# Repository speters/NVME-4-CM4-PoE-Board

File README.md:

# CM4-IO-POE-4G PCIEx1 to NVME Adapter

This is an NVME (M-key) adapter board for the PCIEx1 slot.

Its PCB is designed with a break-away section for the fingered connector. This is then soldered in a matching slot of the PCB to form a 90 degree connector.

## Revisions

 * 0.9.0 added oscillator for 32.768kHz SUSClk signal

 * 0.8.2 finger board improvements, minor size adjustments

 * 0.8.1 working version, gone into small production run

## Description

PCB of the 0.8.2 version without SUSClk

It is designed to fit the [Waveshare CM4G-IO-POE-4G-BOX](https://www.waveshare.com/wiki/Compute_Module_4_PoE_4G_Board#Isolation_GPIO.2FI2C).

## Building

The PCB is cost-optimized to be produced by services like JLCPCB.

You have to separate the finger board from the PCB and solder it into its slot.
Make sure the finger board is at right angles to the main PCB when soldering.

An NVME M-key connector, a standoff, and screw for mounting the NVME has to be provided.
It is recommended to fix the board to the CM4 board with standoffs, not rely solely on the PCIEx1 connector to hold everything in place. For doing this, there are two holes matching holes in the baseboard PCB.

The adapter seems to work fine on the CM4 board without fitting the passives (capacitors and LED).

Remember that your kernel needs PCIe support. There is a convenient [docker cross-compile environment by Jeff Geerling](https://github.com/geerlingguy/raspberry-pi-pcie-devices/tree/master/extras/cross-compile).

## Improvement ideas

 * choose gold fingers for production (I went as cheap as possible with HASL)

 * get out of the way for the CAM0 FPC cable

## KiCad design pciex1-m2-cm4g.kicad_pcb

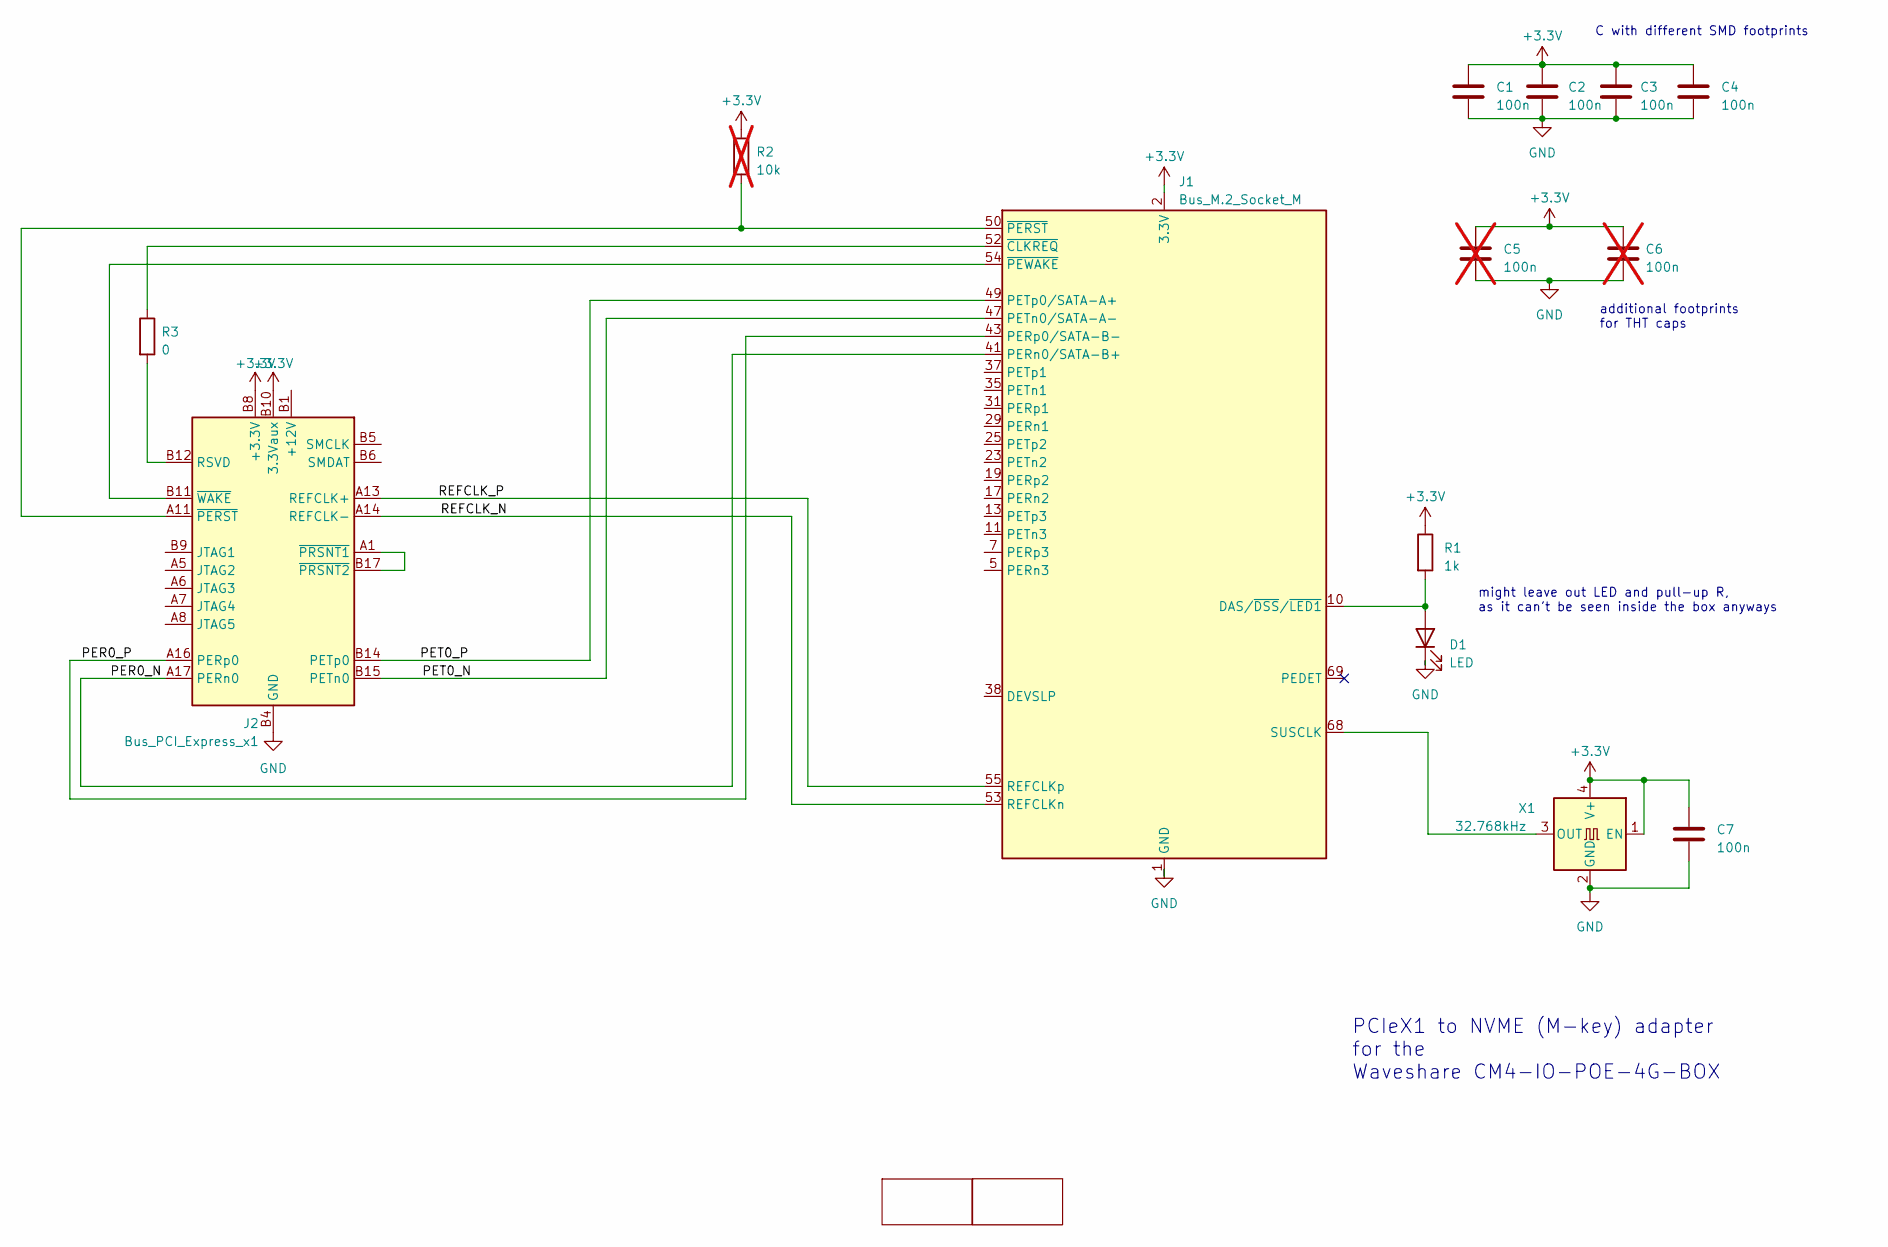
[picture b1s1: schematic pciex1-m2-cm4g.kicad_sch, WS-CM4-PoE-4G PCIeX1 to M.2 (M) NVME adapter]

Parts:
C1, C2, C3, C7: 100n; C_1206_3216Metric
C4: 100n; C_0603_1608Metric
C5, C6: 100n; C_Disc_D3.0mm_W1.6mm_P2.50mm; not fitted
D1: LED; LED_0805_2012Metric
J1: Bus_M.2_Socket_M; TE_1-2199230-6 M2 2280; PartGroup Card Edge Connectors; JLCPCB C841651
J2: Bus_PCI_Express_x1; BUS_PCIexpress_x1 hor_1
R1: 1k; R_0603_1608Metric
R2: 10k; R_0603_1608Metric; not fitted
R3: 0; R_0603_1608Metric
X1: 32.768kHz; Oscillator_SMD_EuroQuartz_XO32-4Pin_3.2x2.5mm; JLCPCB C2901582

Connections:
+3.3V: C1.1, C2.1, C3.1, C4.1, C5.1, C6.1, C7.1, J1.2 (3.3V), J1.4 (3.3V), J1.12 (3.3V), J1.14 (3.3V), J1.16 (3.3V), J1.18 (3.3V), J1.70 (3.3V), J1.72 (3.3V), J1.74 (3.3V), J2.A9 (+3.3V), J2.A10 (+3.3V), J2.B8 (+3.3V), J2.B10 (3.3Vaux), R1.1, R2.1, X1.1 (EN), X1.4 (V+); also elsewhere on the board
/PER0_N: J1.41 (PERn0/SATA-B+), J2.A17 (PERn0)
/PER0_P: J1.43 (PERp0/SATA-B-), J2.A16 (PERp0)
/PET0_N: J1.47 (PETn0/SATA-A-), J2.B15 (PETn0)
/PET0_P: J1.49 (PETp0/SATA-A+), J2.B14 (PETp0)
/REFCLK_N: J1.53 (REFCLKn), J2.A14 (REFCLK-)
/REFCLK_P: J1.55 (REFCLKp), J2.A13 (REFCLK+)
GND: C1.2, C2.2, C3.2, C4.2, C5.2, C6.2, C7.2, D1.1 (K), J1.1 (GND), J1.3 (GND), J1.9 (GND), J1.15 (GND), J1.21 (GND), J1.27 (GND), J1.33 (GND), J1.39 (GND), J1.45 (GND), J1.51 (GND), J1.57 (GND), J1.71 (GND), J1.73 (GND), J1.75 (GND), J2.A4 (GND), J2.A12 (GND), J2.A15 (GND), J2.A18 (GND), J2.B4 (GND), J2.B7 (GND), J2.B13 (GND), J2.B16 (GND), J2.B18 (GND), X1.2 (GND); also elsewhere on the board
unnamed: D1.2 (A), J1.10 (DAS/~DSS/~LED1), R1.2
unnamed: J1.68 (SUSCLK), X1.3 (OUT)
unnamed: J1.52 (~CLKREQ), R3.1
unnamed: J1.50 (~PERST), J2.A11 (~PERST), R2.2
unnamed: J1.54 (~PEWAKE), J2.B11 (~WAKE)
unnamed: J2.A2 (+12V), J2.A3 (+12V), J2.B1 (+12V), J2.B2 (+12V), J2.B3 (+12V)
unnamed: J2.B12 (RSVD), R3.2
unnamed: J2.A1 (~PRSNT1), J2.B17 (~PRSNT2)

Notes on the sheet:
C with different SMD footprints
PCIeX1 to NVME (M-key) adapter for the Waveshare CM4-IO-POE-4G-BOX
additional footprints for THT caps
might leave out LED and pull-up R, as it can't be seen inside the box anyways

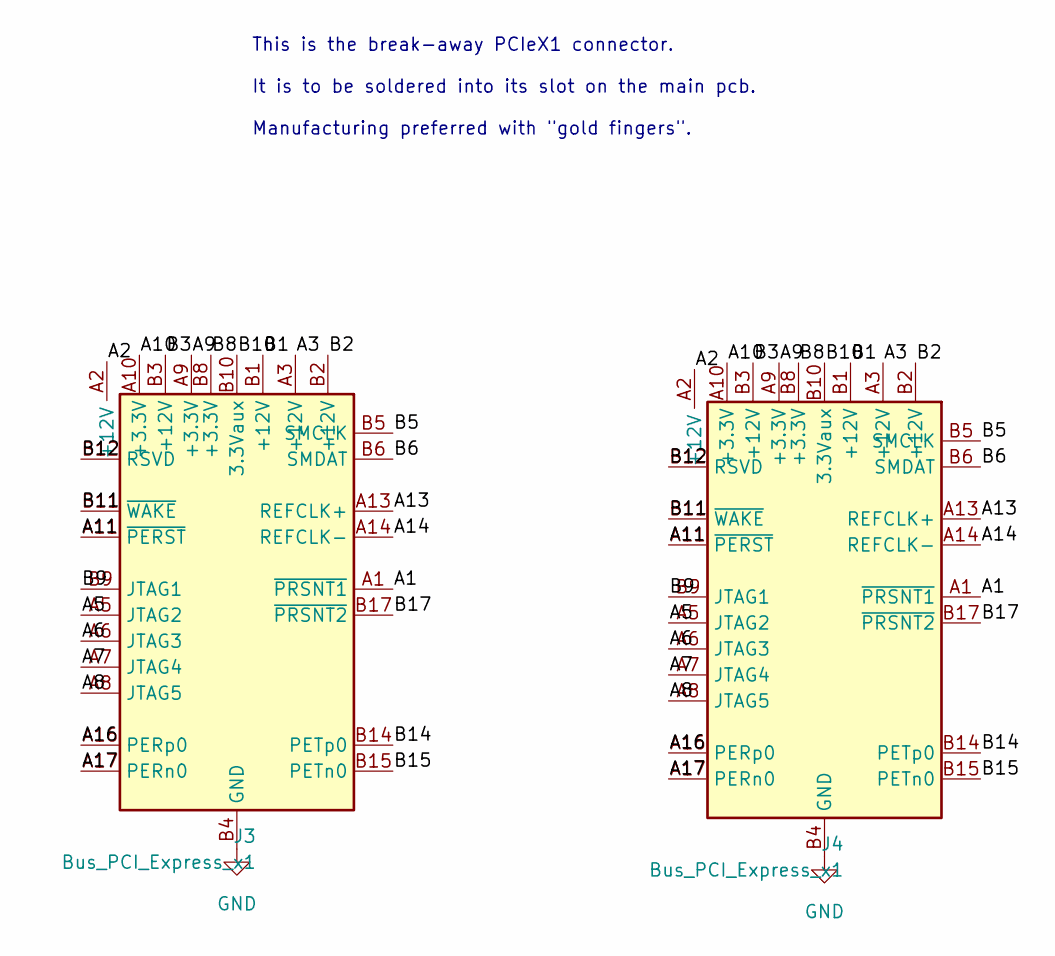
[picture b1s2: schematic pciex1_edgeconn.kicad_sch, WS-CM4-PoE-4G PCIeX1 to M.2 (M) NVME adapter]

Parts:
J3: Bus_PCI_Express_x1; BUS_PCIexpress_x1
J4: Bus_PCI_Express_x1; BUS_PCIexpress_x1 SOLDER

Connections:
/pciex1_edgeconn/A1: J3.A1 (~PRSNT1), J4.A1 (~PRSNT1)
/pciex1_edgeconn/A2: J3.A2 (+12V), J4.A2 (+12V)
/pciex1_edgeconn/A3: J3.A3 (+12V), J4.A3 (+12V)
/pciex1_edgeconn/A5: J3.A5 (JTAG2), J4.A5 (JTAG2)
/pciex1_edgeconn/A6: J3.A6 (JTAG3), J4.A6 (JTAG3)
/pciex1_edgeconn/A7: J3.A7 (JTAG4), J4.A7 (JTAG4)
/pciex1_edgeconn/A8: J3.A8 (JTAG5), J4.A8 (JTAG5)
/pciex1_edgeconn/A9: J3.A9 (+3.3V), J4.A9 (+3.3V)
/pciex1_edgeconn/A10: J3.A10 (+3.3V), J4.A10 (+3.3V)
/pciex1_edgeconn/A11: J3.A11 (~PERST), J4.A11 (~PERST)
/pciex1_edgeconn/A13: J3.A13 (REFCLK+), J4.A13 (REFCLK+)
/pciex1_edgeconn/A14: J3.A14 (REFCLK-), J4.A14 (REFCLK-)
/pciex1_edgeconn/A16: J3.A16 (PERp0), J4.A16 (PERp0)
/pciex1_edgeconn/A17: J3.A17 (PERn0), J4.A17 (PERn0)
/pciex1_edgeconn/B1: J3.B1 (+12V), J4.B1 (+12V)
/pciex1_edgeconn/B2: J3.B2 (+12V), J4.B2 (+12V)
/pciex1_edgeconn/B3: J3.B3 (+12V), J4.B3 (+12V)
/pciex1_edgeconn/B5: J3.B5 (SMCLK), J4.B5 (SMCLK)
/pciex1_edgeconn/B6: J3.B6 (SMDAT), J4.B6 (SMDAT)
/pciex1_edgeconn/B8: J3.B8 (+3.3V), J4.B8 (+3.3V)
/pciex1_edgeconn/B9: J3.B9 (JTAG1), J4.B9 (JTAG1)
/pciex1_edgeconn/B10: J3.B10 (3.3Vaux), J4.B10 (3.3Vaux)
/pciex1_edgeconn/B11: J3.B11 (~WAKE), J4.B11 (~WAKE)
/pciex1_edgeconn/B12: J3.B12 (RSVD), J4.B12 (RSVD)
/pciex1_edgeconn/B14: J3.B14 (PETp0), J4.B14 (PETp0)
/pciex1_edgeconn/B15: J3.B15 (PETn0), J4.B15 (PETn0)
/pciex1_edgeconn/B17: J3.B17 (~PRSNT2), J4.B17 (~PRSNT2)
GND: J3.A4 (GND), J3.A12 (GND), J3.A15 (GND), J3.A18 (GND), J3.B4 (GND), J3.B7 (GND), J3.B13 (GND), J3.B16 (GND), J3.B18 (GND), J4.A4 (GND), J4.A12 (GND), J4.A15 (GND), J4.A18 (GND), J4.B4 (GND), J4.B7 (GND), J4.B13 (GND), J4.B16 (GND), J4.B18 (GND); also elsewhere on the board

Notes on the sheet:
This is the break-away PCIeX1 connector. It is to be soldered into its slot on the main pcb. Manufacturing preferred with "gold fingers".

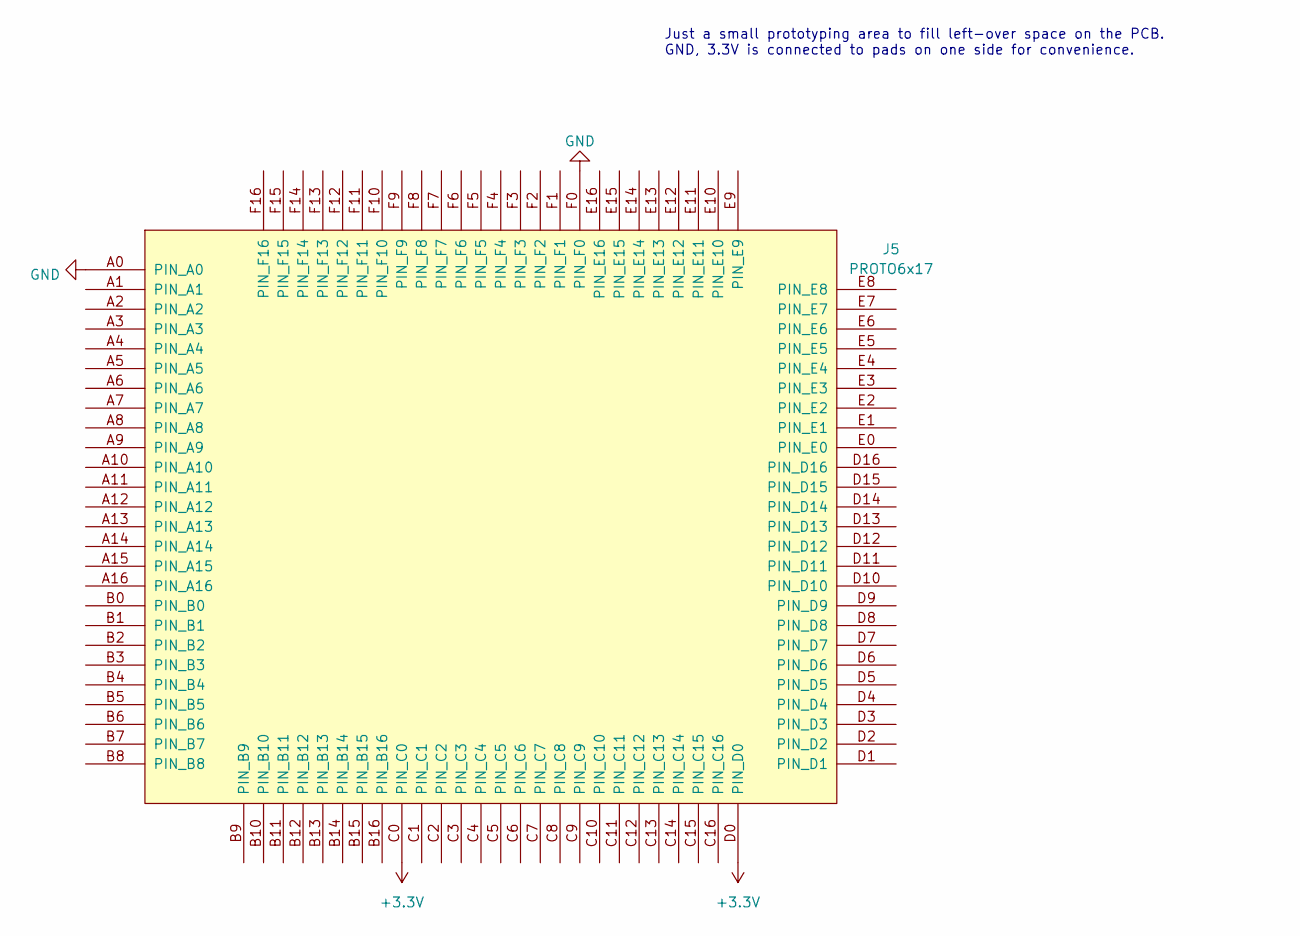
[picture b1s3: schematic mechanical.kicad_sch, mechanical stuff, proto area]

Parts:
J5: PROTO6x17; proto112 127

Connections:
+3.3V: J5.C0 (PIN), J5.D0 (PIN); also elsewhere on the board
GND: J5.A0 (PIN), J5.F0 (PIN); also elsewhere on the board

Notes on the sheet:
Just a small prototyping area to fill left-over space on the PCB. GND, 3.3V is connected to pads on one side for convenience.

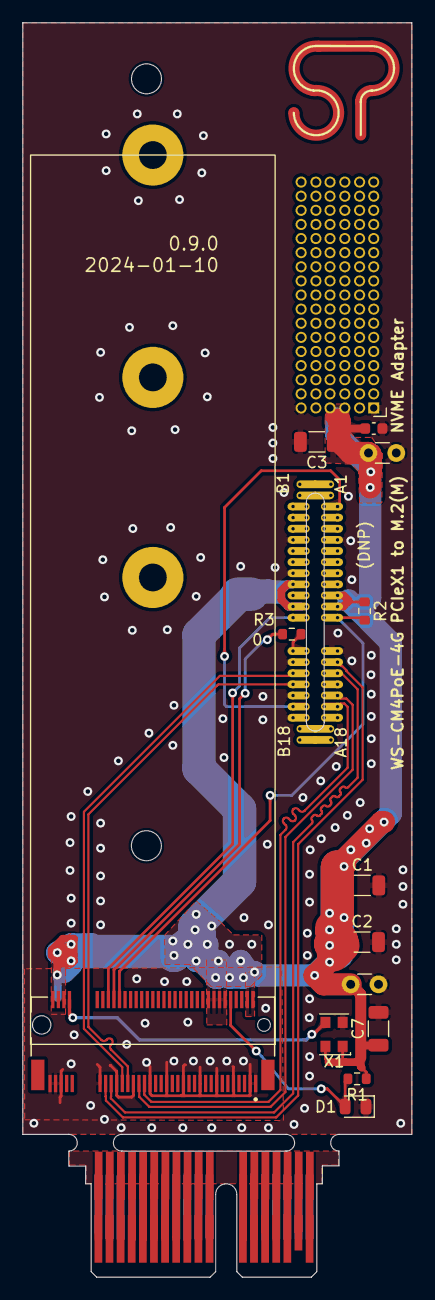
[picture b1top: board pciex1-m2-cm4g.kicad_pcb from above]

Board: 2 copper layers, 35.0 x 112.8 mm, 20 parts (0 on the bottom side), 43 nets.

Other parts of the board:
Hole1, Hole2: MountingHole_2.7mm_M2.5_DIN965
Logo: SP_Logo_10mm

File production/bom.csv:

Designator,Footprint,Quantity,Value,LCSC Part #
C1,1206,1,100n,
C2,1206,1,100n,
C3,1206,1,100n,
C4,0603,1,100n,
"C5, C6",C_Disc_D3.0mm_W1.6mm_P2.50mm,2,100n,
C7,1206,1,100n,
D1,0805,1,LED,
J1,TE_1-2199230-6 M2 2280,1,Bus_M.2_Socket_M,
J2,BUS_PCIexpress_x1 hor_1,1,Bus_PCI_Express_x1,
J3,BUS_PCIexpress_x1,1,Bus_PCI_Express_x1,
J4,BUS_PCIexpress_x1 SOLDER,1,Bus_PCI_Express_x1,
J5,proto112 127,1,PROTO6x17,
R1,0603,1,1k,
R2,0603,1,10k,
R3,0603,1,0,
X1,Oscillator_SMD_EuroQuartz_XO32-4Pin_3.2x2.5mm,1,32.768kHz,

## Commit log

2023-04-01 initial import
2023-04-01 pictures of pcb and photo
2023-04-01 docs
2023-04-01 pcb preview image
2023-04-01 added schematic preview
2023-04-01 soldering tip
2023-04-01 improvement idea
2023-04-01 clearifications
2023-04-03 standoff holes mentioned
2023-04-21 Typo fix
2024-01-10 added SUSClk
2024-01-10 descriptioN
